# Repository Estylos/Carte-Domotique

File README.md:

# Carte de contrôle domotique avec ESP32

Ce projet prend place dans le cadre de mon stage de fin de 1ère année de cycle ingénieur à l'école Grenoble INP - Esisar, effectué dans le bureau d'études en conception électronique [IE-Concept](https://www.ie-concept.fr/). Un grand merci à l'entreprise de m'avoir permis d'effectuer ce stage dans d'excellentes conditions ainsi que d'autoriser la publication du travail que j'ai pu mener.

## Présentation

L'objectif de ce stage consistait à l'installation d'un système domotique permettant de contrôler les climatiseurs de la société, ainsi que monitorer différents capteurs (température, humidité, présence…) le tout depuis Home Assistant. Ce repo contient seulement la carte électronique basée sur un ESP32 DevKit V1, réalisé sur KiCad ainsi que son boîtier modélisé sur Fusion 360.  

## Objectifs de la carte

La carte domotique conçue permet le branchement de 4 rubans ou anneaux de LEDs adressables WS2812 (pour l'indication lumineuse allant avec le contrôle des clims), 4 LEDs infrarouges, 2 sorties PWM, 1 sortie I2C, 2 relais, 1 port divers avec deux sources de tension (5 et 3.3V) et 2 GPIOs (utilisables par l’ADC1 de l’ESP32). La carte permet aussi le branchement d'un DFPlayer Mini et d'un haut-parleur servant à la lecture de sons depuis une carte SD (et pilotable par Home Assistant).

L'ESP32 peut être configuré directement avec ESPHome, permettant une intégration directe avec Home Assistant. 

## Circuit

Le circuit n'est pas d'une grande complexité. Il s'agit globalement d'un ESP32 avec des borniers à vis, 2 relais, un DFPlayer et quelques composants passifs : condensateurs pour le découplage et résistances pour la limitation de courant. Un réseau de transistors Darlington (ULN2003A) est utilisé afin d'amplifier et de monter à 5V les sorties des LEDs infrarouges contrôlant les climatiseurs et les sorties pour les 2 relais.

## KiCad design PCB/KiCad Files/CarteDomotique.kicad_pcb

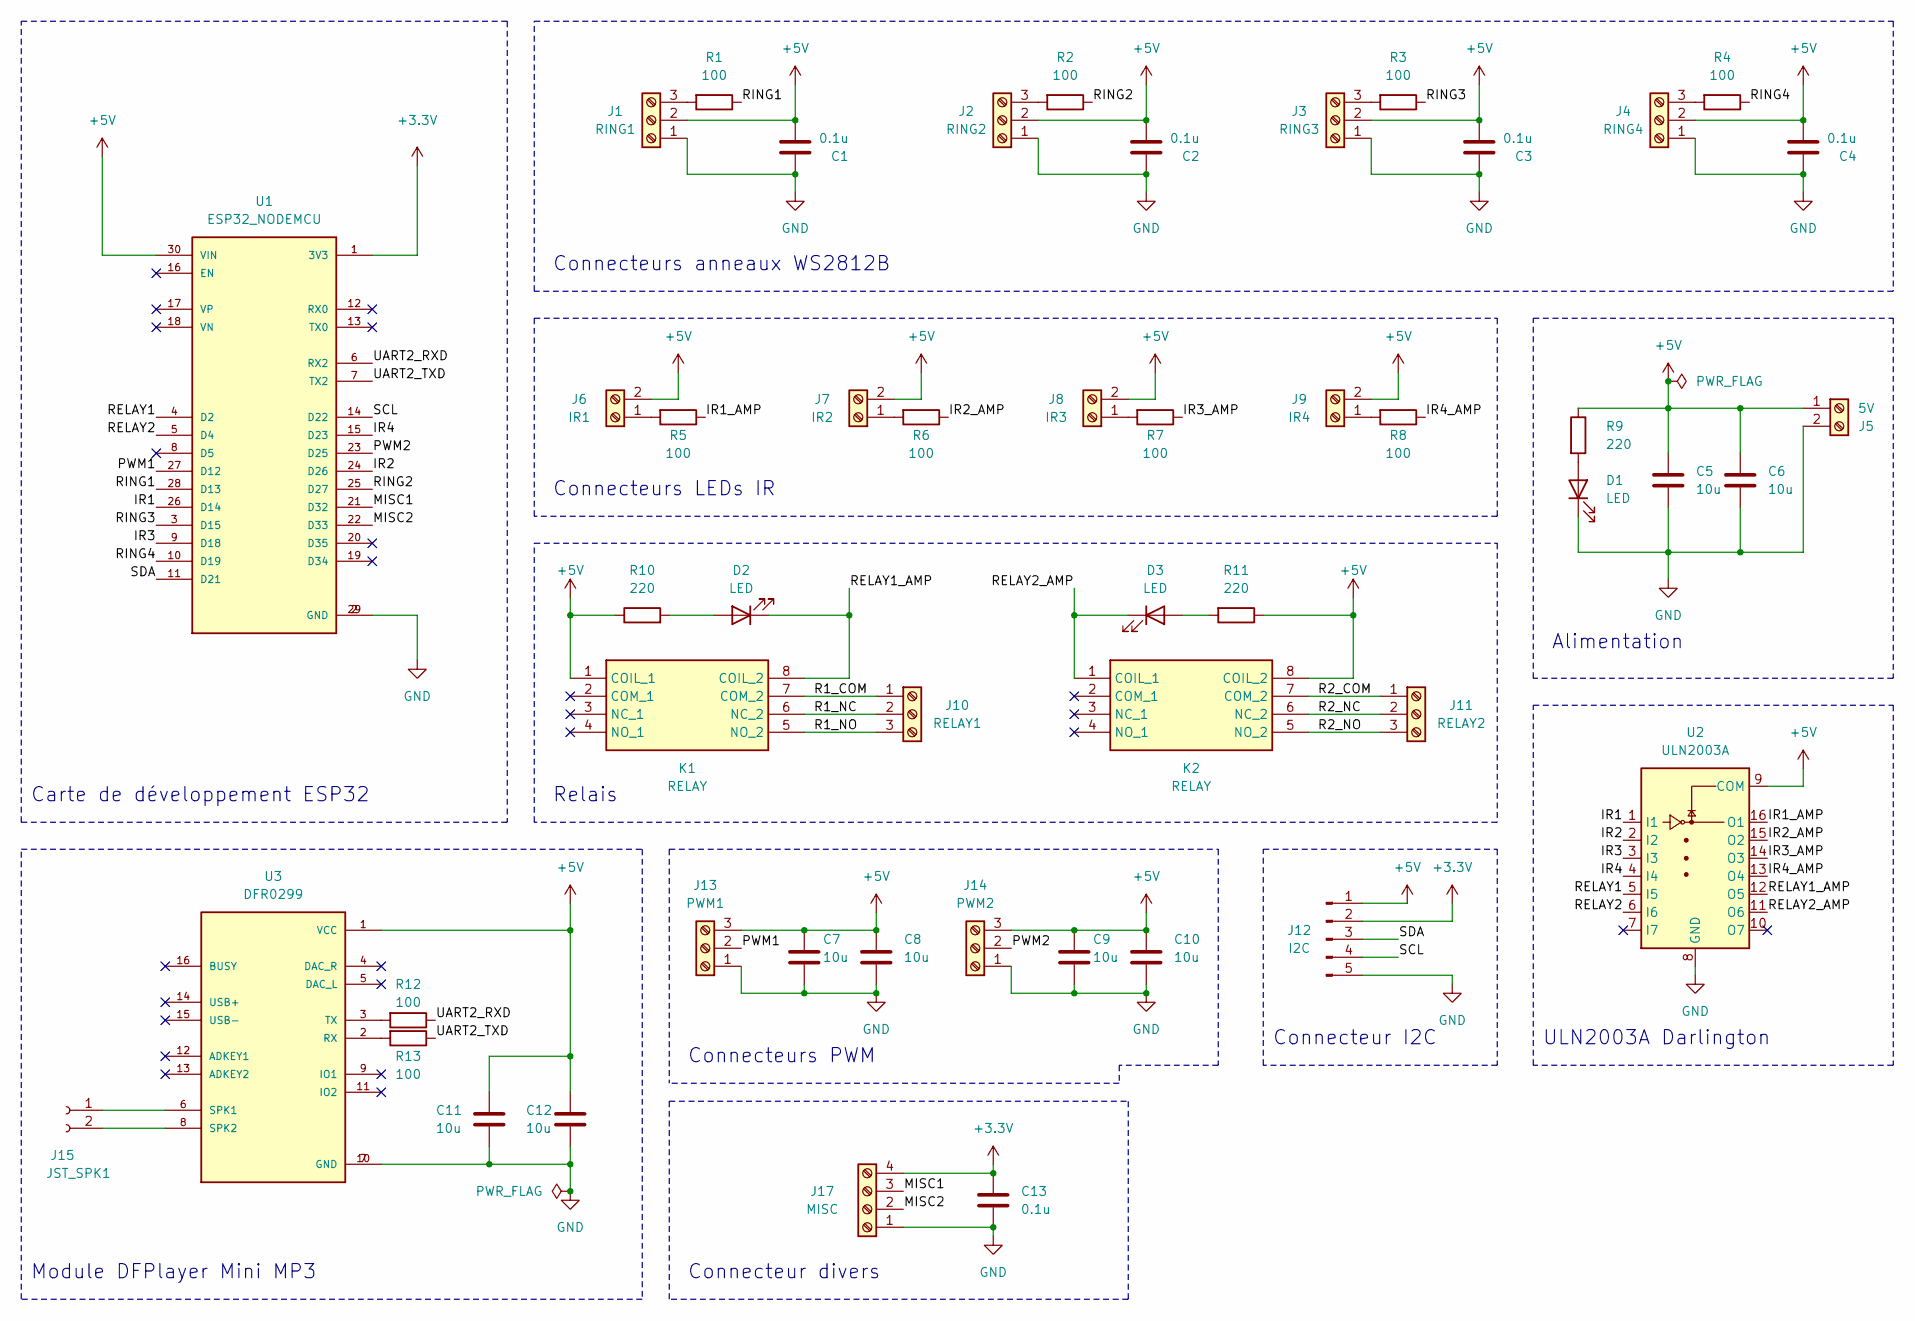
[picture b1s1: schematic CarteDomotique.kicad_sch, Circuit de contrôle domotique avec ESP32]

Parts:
C1, C2, C3, C4, C13: 0.1u; C_0603_1608Metric_Pad1.08x0.95mm_HandSolder; LCSC Part C14665
C5, C6, C7, C8, C9, C10, C11, C12: 10u; C_0603_1608Metric_Pad1.08x0.95mm_HandSolder; Farnell 9452176
D1, D2, D3: LED; LED_0603_1608Metric_Pad1.05x0.95mm_HandSolder; LCSC Part C84263
J1: RING1; TerminalBlock_bornier-3_P5.08mm; LCSC Part C72334
J2: RING2; TerminalBlock_bornier-3_P5.08mm; LCSC Part C72334
J3: RING3; TerminalBlock_bornier-3_P5.08mm; LCSC Part C72334
J4: RING4; TerminalBlock_bornier-3_P5.08mm; LCSC Part C72334
J5: 5V; TerminalBlock_bornier-2_P5.08mm; LCSC Part C8465
J6: IR1; TerminalBlock_bornier-2_P5.08mm; LCSC Part C8465
J7: IR2; TerminalBlock_bornier-2_P5.08mm; LCSC Part C8465
J8: IR3; TerminalBlock_bornier-2_P5.08mm; LCSC Part C8465
J9: IR4; TerminalBlock_bornier-2_P5.08mm; LCSC Part C8465
J10: RELAY1; TerminalBlock_bornier-3_P5.08mm; LCSC Part C72334
J11: RELAY2; TerminalBlock_bornier-3_P5.08mm; LCSC Part C72334
J12: I2C; PinHeader_1x05_P2.54mm_Vertical; LCSC Part C492404
J13: PWM1; TerminalBlock_bornier-3_P5.08mm; LCSC Part C72334
J14: PWM2; TerminalBlock_bornier-3_P5.08mm; LCSC Part C72334
J15: JST_SPK1; JST_PH_B2B-PH-K_1x02_P2.00mm_Vertical; Farnell 9492534
J17: MISC; TerminalBlock_bornier-4_P5.08mm; LCSC Part C2915641
K1, K2: RELAY; J104D2C24VDC20S; Manufacturer_Part_Number J104D2C24VDC.20S; Digi-Key 2449-J104D2C5VDC.20S-ND
R1, R2, R3, R4, R12, R13: 100; R_0603_1608Metric_Pad0.98x0.95mm_HandSolder; LCSC Part C22775
R5, R6, R7, R8: 100; R_0603_1608Metric_Pad0.98x0.95mm_HandSolder; LCSC Part C107696
R9, R10, R11: 220; R_0603_1608Metric_Pad0.98x0.95mm_HandSolder; LCSC Part C107696
U1: ESP32_NODEMCU; MODULE_ESP32_DEVKIT_V1; PARTREV N/A; JLCPCB BOM 0
U2: ULN2003A; SOIC-16_3.9x9.9mm_P1.27mm; Farnell 2628016
U3: DFR0299; MODULE_DFR0299; JLCPCB BOM 0

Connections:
+3.3V: C13.1, J12.2, J17.4, U1.1 (3V3)
+5V: C1.1, C2.1, C3.1, C4.1, C5.1, C6.1, C7.1, C8.1, C9.1, C10.1, C11.1, C12.1, J1.2, J2.2, J3.2, J4.2, J5.1, J6.2, J7.2, J8.2, J9.2, J12.1, J13.3, J14.3, K1.1 (COIL_1), K2.8 (COIL_2), R9.1, R10.1, R11.1, U1.30 (VIN), U2.9 (COM), U3.1 (VCC)
/IR1: U1.26 (D14), U2.1 (I1)
/IR1_AMP: R5.1, U2.16 (O1)
/IR2: U1.24 (D26), U2.2 (I2)
/IR2_AMP: R6.1, U2.15 (O2)
/IR3: U1.9 (D18), U2.3 (I3)
/IR3_AMP: R7.1, U2.14 (O3)
/IR4: U1.15 (D23), U2.4 (I4)
/IR4_AMP: R8.1, U2.13 (O4)
/MISC1: J17.3, U1.21 (D32)
/MISC2: J17.2, U1.22 (D33)
/PWM1: J13.2, U1.27 (D12)
/PWM2: J14.2, U1.23 (D25)
/R1_COM: J10.1, K1.7 (COM_2)
/R1_NC: J10.2, K1.6 (NC_2)
/R1_NO: J10.3, K1.5 (NO_2)
/R2_COM: J11.1, K2.7 (COM_2)
/R2_NC: J11.2, K2.6 (NC_2)
/R2_NO: J11.3, K2.5 (NO_2)
/RELAY1: U1.4 (D2), U2.5 (I5)
/RELAY1_AMP: D2.1 (K), K1.8 (COIL_2), U2.12 (O5)
/RELAY2: U1.5 (D4), U2.6 (I6)
/RELAY2_AMP: D3.1 (K), K2.1 (COIL_1), U2.11 (O6)
/RING1: R1.1, U1.28 (D13)
/RING2: R2.1, U1.25 (D27)
/RING3: R3.1, U1.3 (D15)
/RING4: R4.1, U1.10 (D19)
/SCL: J12.4, U1.14 (D22)
/SDA: J12.3, U1.11 (D21)
/UART2_RXD: R12.1, U1.6 (RX2)
/UART2_TXD: R13.1, U1.7 (TX2)
GND: C1.2, C2.2, C3.2, C4.2, C5.2, C6.2, C7.2, C8.2, C9.2, C10.2, C11.2, C12.2, C13.2, D1.1 (K), J1.1, J2.1, J3.1, J4.1, J5.2, J12.5, J13.1, J14.1, J17.1, U1.2 (GND), U1.29 (GND), U2.8 (GND), U3.7 (GND), U3.10 (GND)
unnamed: D1.2 (A), R9.2
unnamed: D2.2 (A), R10.2
unnamed: D3.2 (A), R11.2
unnamed: J1.3, R1.2
unnamed: J2.3, R2.2
unnamed: J3.3, R3.2
unnamed: J4.3, R4.2
unnamed: J6.1, R5.2
unnamed: J7.1, R6.2
unnamed: J8.1, R7.2
unnamed: J9.1, R8.2
unnamed: J15.1, U3.6 (SPK1)
unnamed: J15.2, U3.8 (SPK2)
unnamed: R13.2, U3.2 (RX)
unnamed: R12.2, U3.3 (TX)

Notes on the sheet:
Alimentation
Carte de développement ESP32
ULN2003A Darlington
Connecteurs PWM
Module DFPlayer Mini MP3
Connecteurs LEDs IR
Connecteur I2C
Relais
Connecteurs anneaux WS2812B
Connecteur divers

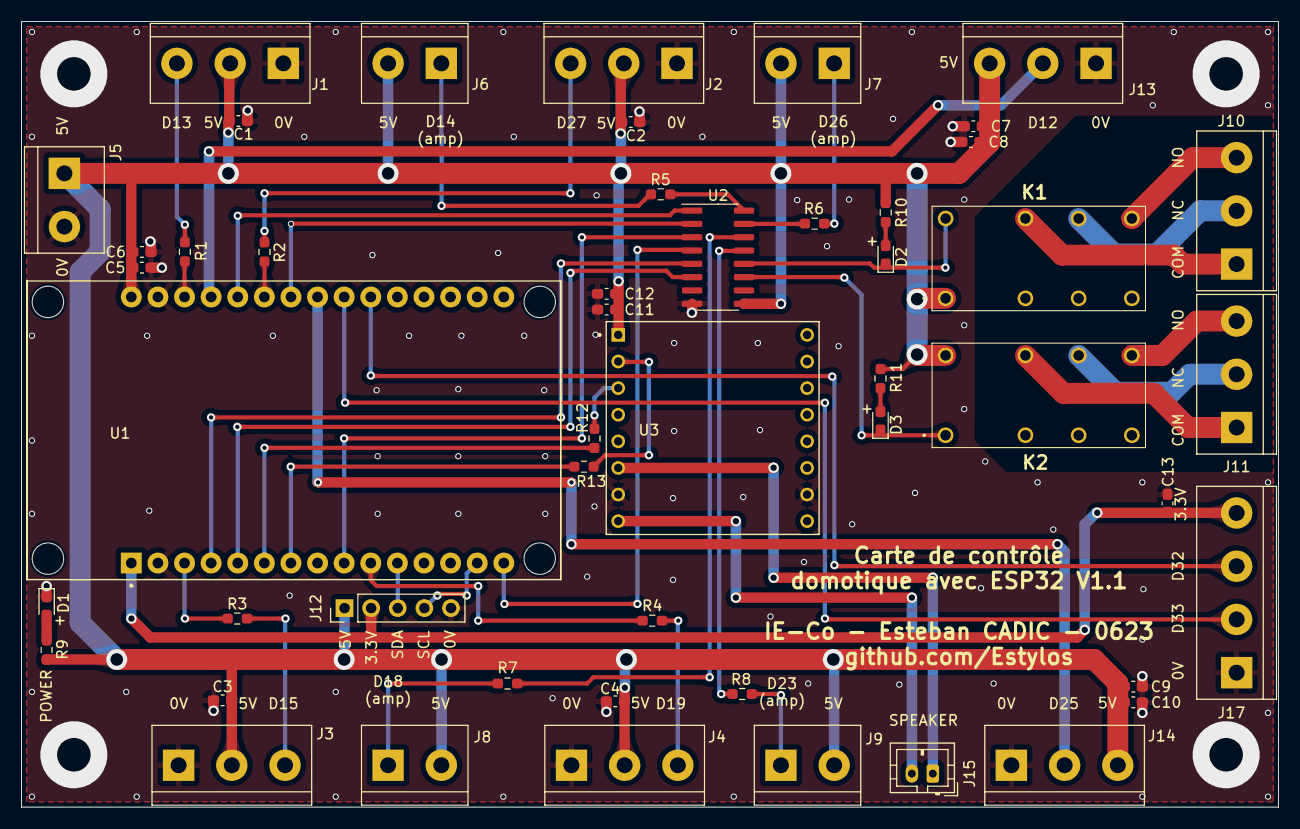
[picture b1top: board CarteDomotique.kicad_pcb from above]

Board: 2 copper layers, 120.0 x 75.0 mm, 50 parts (0 on the bottom side), 48 nets.

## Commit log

2023-07-18 Init commit
